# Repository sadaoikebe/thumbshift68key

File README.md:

## TS69 親指シフト入力用 68% キーボード

分割3uスペースキーをもつ 68% キーボード  

## 必要なもの

* 基板 (製造サービスなどに発注)
* Pro Micro
* ピンヘッダ12ピン×2
* 6x 鬼目ナットM3 Aタイプ(打ち込み) 深さ5.5mm [モノタロウ](https://www.monotaro.com/p/4175/4824/)
* 6x M3キャップボルト [モノタロウ](https://www.monotaro.com/p/2901/7687/)
* 69x キースイッチ
* スタビライザー (3x2u, 2x3u)
* キーキャップ 2x 3uスペース
* ガスケット (4mm幅×2mm厚のPoronやEVAフォームなどを貼る)
* ケース 3Dプリンタ [データ](case/)
* 定位板 3Dプリンタ もしくは業者にレーザーカッティングをお願いする [データ](plate/)

Pro Microは同等品のType-Cやコンスルー版などのほうが良いかも。MicroUSB版を使うならばコネクタモゲないようにエポキシ接着剤などで補強したほうがよい  

## 製造工程

Pro Microを裏側実装する関係で、実装の順番を間違えると面倒なことになる  
1. 基板にスタビライザーを取り付け
2. 基板にピンヘッダを半田付け
3. 周辺部分のキースイッチを取り付け
4. スタビライザーの動作確認 キースイッチを取り付けてキーキャップを実際に被せてスタビライザーが気持ちよく動くか確認。プレートの精度が十分よければこの手順は必要ないけど、3Dプリンタでプレートを自作する場合、しばしばスタビライザー軸が端に触れて動きが悪くなることがある。もし動きが悪い場合プレートの精度を見直すか、あるいはスタビライザーの動作が悪いキーが嵌まる部分のプレートを削って広げて遊びを作る。
5. キースイッチを全部取り付け
6. Pro Microを取り付け
7. キーキャップを取り付け
8. ケースに入れる

## キー配置

バックスペースキーの部分だけカスタマイズ可能だがそれ以外は固定。  
バックスペースキーの場所には2つのキーを割り当てて H*KBのような配置にすることもできる。  
今後親指キーに3u以外(2.75u, 2.25uなど) も使えるようにしたバージョンを作りたかったりはする。

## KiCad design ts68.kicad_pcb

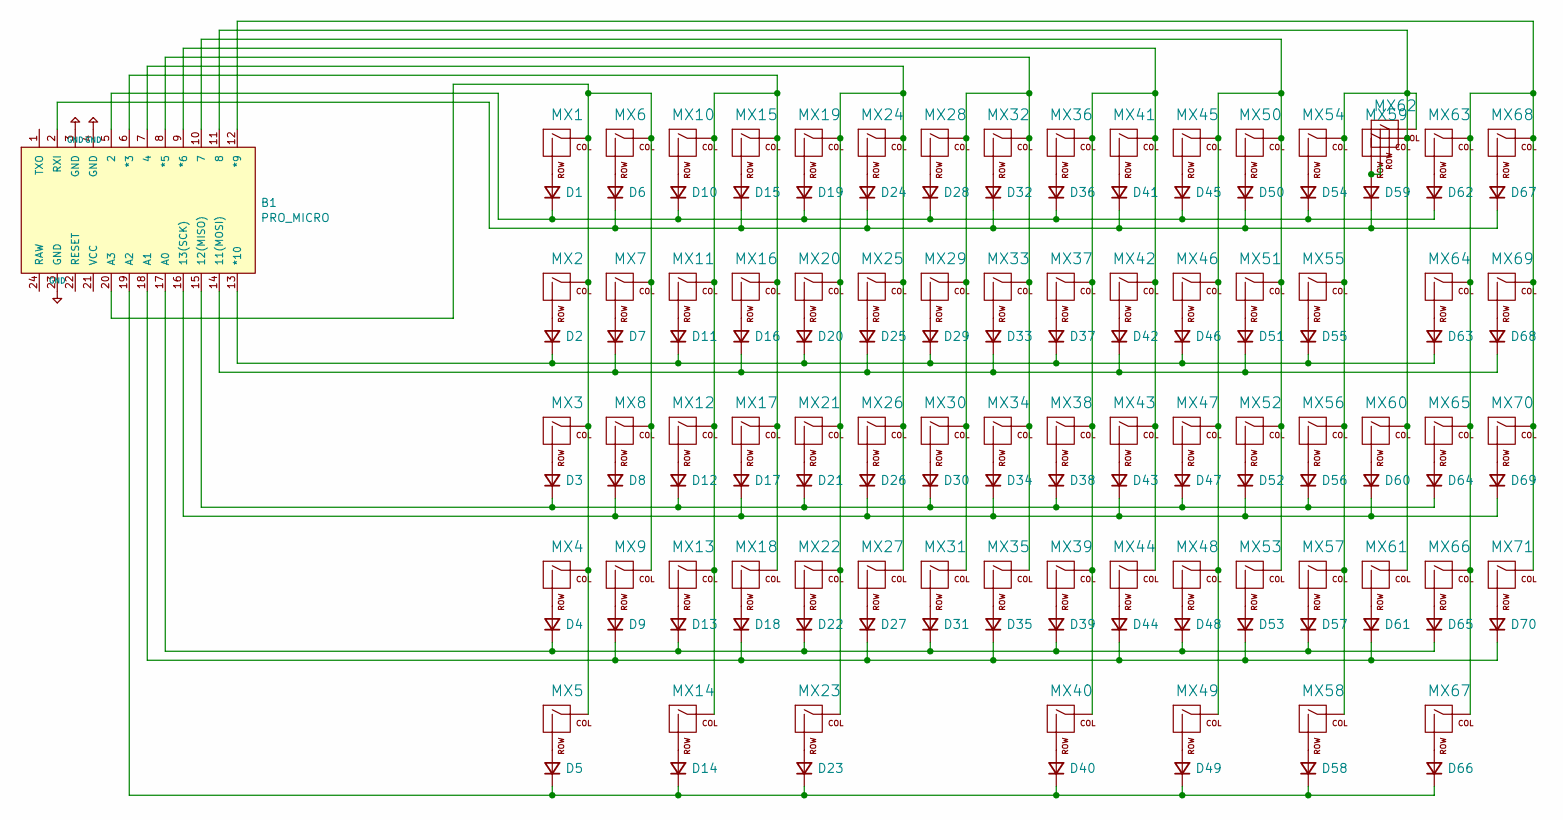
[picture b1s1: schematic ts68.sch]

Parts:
B1: PRO_MICRO; SPARKFUN_PRO_MICRO
D1, D2, D3, D4, D5, D6, D7, D8, D9, D10, D11, D12, D13, D14, D15, D16, D17, D18, D19, D20, D21, D22, D23, D24, D25, D26, D27, D28, D29, D30, D31, D32, D33, D34, D35, D36, D37, D38, D39, D40, D41, D42, D43, D44, D45, D46, D47, D48, D49, D50, D51, D52, D53, D54, D55, D56, D57, D58, D59, D60, D61, D62, D63, D64, D65, D66, D67, D68, D69, D70: D; D_SOD-123
MX1, MX6, MX7, MX8, MX10, MX11, MX12, MX13, MX15, MX16, MX17, MX18, MX19, MX20, MX21, MX22, MX24, MX25, MX26, MX27, MX28, MX29, MX30, MX31, MX32, MX33, MX34, MX35, MX36, MX37, MX38, MX39, MX41, MX42, MX43, MX44, MX45, MX46, MX47, MX48, MX50, MX51, MX52, MX53, MX54, MX55, MX56, MX58, MX59, MX61, MX63, MX65, MX66, MX67, MX68, MX69, MX70, MX71: MX-NoLED; MXOnly-1U-NoLED
MX2, MX64: MX-NoLED; MXOnly-1.5U-NoLED
MX3, MX57: MX-NoLED; MXOnly-1.75U-NoLED
MX4, MX60: MX-NoLED; MXOnly-2.25U-NoLED
MX5, MX9, MX14, MX49: MX-NoLED; MXOnly-1.25U-NoLED
MX23, MX40: MX-NoLED; MXOnly-3U-ReversedStabilizers-NoLED
MX62: MX-NoLED; MXOnly-2U-NoLED

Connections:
+5V: B1.3 (GND), B1.4 (GND), B1.23 (GND)
unnamed: B1.2 (RXI), D6.1 (K), D15.1 (K), D24.1 (K), D32.1 (K), D41.1 (K), D50.1 (K), D59.1 (K), D67.1 (K)
unnamed: B1.5 (2), D1.1 (K), D10.1 (K), D19.1 (K), D28.1 (K), D36.1 (K), D45.1 (K), D54.1 (K), D62.1 (K)
unnamed: B1.6 (*3), MX10.1 (COL), MX11.1 (COL), MX12.1 (COL), MX13.1 (COL), MX14.1 (COL), MX15.1 (COL), MX16.1 (COL), MX17.1 (COL), MX18.1 (COL)
unnamed: B1.7 (4), MX19.1 (COL), MX20.1 (COL), MX21.1 (COL), MX22.1 (COL), MX23.1 (COL), MX24.1 (COL), MX25.1 (COL), MX26.1 (COL), MX27.1 (COL)
unnamed: B1.8 (*5), MX28.1 (COL), MX29.1 (COL), MX30.1 (COL), MX31.1 (COL), MX32.1 (COL), MX33.1 (COL), MX34.1 (COL), MX35.1 (COL)
unnamed: B1.9 (*6), MX36.1 (COL), MX37.1 (COL), MX38.1 (COL), MX39.1 (COL), MX40.1 (COL), MX41.1 (COL), MX42.1 (COL), MX43.1 (COL), MX44.1 (COL)
unnamed: B1.10 (7), MX45.1 (COL), MX46.1 (COL), MX47.1 (COL), MX48.1 (COL), MX49.1 (COL), MX50.1 (COL), MX51.1 (COL), MX52.1 (COL), MX53.1 (COL)
unnamed: B1.11 (8), MX54.1 (COL), MX55.1 (COL), MX56.1 (COL), MX57.1 (COL), MX58.1 (COL), MX59.1 (COL), MX60.1 (COL), MX61.1 (COL), MX62.1 (COL)
unnamed: B1.12 (*9), MX63.1 (COL), MX64.1 (COL), MX65.1 (COL), MX66.1 (COL), MX67.1 (COL), MX68.1 (COL), MX69.1 (COL), MX70.1 (COL), MX71.1 (COL)
unnamed: B1.13 (*10), D2.1 (K), D11.1 (K), D20.1 (K), D29.1 (K), D37.1 (K), D46.1 (K), D55.1 (K), D63.1 (K)
unnamed: B1.14 (11(MOSI)), D7.1 (K), D16.1 (K), D25.1 (K), D33.1 (K), D42.1 (K), D51.1 (K), D68.1 (K)
unnamed: B1.15 (12(MISO)), D3.1 (K), D12.1 (K), D21.1 (K), D30.1 (K), D38.1 (K), D47.1 (K), D56.1 (K), D64.1 (K)
unnamed: B1.16 (13(SCK)), D8.1 (K), D17.1 (K), D26.1 (K), D34.1 (K), D43.1 (K), D52.1 (K), D60.1 (K), D69.1 (K)
unnamed: B1.17 (A0), D4.1 (K), D13.1 (K), D22.1 (K), D31.1 (K), D39.1 (K), D48.1 (K), D57.1 (K), D65.1 (K)
unnamed: B1.18 (A1), D9.1 (K), D18.1 (K), D27.1 (K), D35.1 (K), D44.1 (K), D53.1 (K), D61.1 (K), D70.1 (K)
unnamed: B1.19 (A2), D5.1 (K), D14.1 (K), D23.1 (K), D40.1 (K), D49.1 (K), D58.1 (K), D66.1 (K)
unnamed: B1.20 (A3), MX1.1 (COL), MX2.1 (COL), MX3.1 (COL), MX4.1 (COL), MX5.1 (COL), MX6.1 (COL), MX7.1 (COL), MX8.1 (COL), MX9.1 (COL)
unnamed: D1.2 (A), MX1.2 (ROW)
unnamed: D2.2 (A), MX2.2 (ROW)
unnamed: D3.2 (A), MX3.2 (ROW)
unnamed: D4.2 (A), MX4.2 (ROW)
unnamed: D5.2 (A), MX5.2 (ROW)
unnamed: D6.2 (A), MX6.2 (ROW)
unnamed: D7.2 (A), MX7.2 (ROW)
unnamed: D8.2 (A), MX8.2 (ROW)
unnamed: D9.2 (A), MX9.2 (ROW)
unnamed: D10.2 (A), MX10.2 (ROW)
unnamed: D11.2 (A), MX11.2 (ROW)
unnamed: D12.2 (A), MX12.2 (ROW)
unnamed: D13.2 (A), MX13.2 (ROW)
unnamed: D14.2 (A), MX14.2 (ROW)
unnamed: D15.2 (A), MX15.2 (ROW)
unnamed: D16.2 (A), MX16.2 (ROW)
unnamed: D17.2 (A), MX17.2 (ROW)
unnamed: D18.2 (A), MX18.2 (ROW)
unnamed: D19.2 (A), MX19.2 (ROW)
unnamed: D20.2 (A), MX20.2 (ROW)
unnamed: D21.2 (A), MX21.2 (ROW)
unnamed: D22.2 (A), MX22.2 (ROW)
unnamed: D23.2 (A), MX23.2 (ROW)
unnamed: D24.2 (A), MX24.2 (ROW)
unnamed: D25.2 (A), MX25.2 (ROW)
unnamed: D26.2 (A), MX26.2 (ROW)
unnamed: D27.2 (A), MX27.2 (ROW)
unnamed: D28.2 (A), MX28.2 (ROW)
unnamed: D29.2 (A), MX29.2 (ROW)
unnamed: D30.2 (A), MX30.2 (ROW)
unnamed: D31.2 (A), MX31.2 (ROW)
unnamed: D32.2 (A), MX32.2 (ROW)
unnamed: D33.2 (A), MX33.2 (ROW)
unnamed: D34.2 (A), MX34.2 (ROW)
unnamed: D35.2 (A), MX35.2 (ROW)
unnamed: D36.2 (A), MX36.2 (ROW)
unnamed: D37.2 (A), MX37.2 (ROW)
unnamed: D38.2 (A), MX38.2 (ROW)
unnamed: D39.2 (A), MX39.2 (ROW)
unnamed: D40.2 (A), MX40.2 (ROW)
unnamed: D41.2 (A), MX41.2 (ROW)
unnamed: D42.2 (A), MX42.2 (ROW)
unnamed: D43.2 (A), MX43.2 (ROW)
unnamed: D44.2 (A), MX44.2 (ROW)
unnamed: D45.2 (A), MX45.2 (ROW)
unnamed: D46.2 (A), MX46.2 (ROW)
unnamed: D47.2 (A), MX47.2 (ROW)
unnamed: D48.2 (A), MX48.2 (ROW)
unnamed: D49.2 (A), MX49.2 (ROW)
unnamed: D50.2 (A), MX50.2 (ROW)
unnamed: D51.2 (A), MX51.2 (ROW)
unnamed: D52.2 (A), MX52.2 (ROW)
unnamed: D53.2 (A), MX53.2 (ROW)
unnamed: D54.2 (A), MX54.2 (ROW)
unnamed: D55.2 (A), MX55.2 (ROW)
unnamed: D56.2 (A), MX56.2 (ROW)
unnamed: D57.2 (A), MX57.2 (ROW)
unnamed: D58.2 (A), MX58.2 (ROW)
unnamed: D59.2 (A), MX59.2 (ROW), MX62.2 (ROW)
unnamed: D60.2 (A), MX60.2 (ROW)
unnamed: D61.2 (A), MX61.2 (ROW)
unnamed: D62.2 (A), MX63.2 (ROW)
unnamed: D63.2 (A), MX64.2 (ROW)
unnamed: D64.2 (A), MX65.2 (ROW)
unnamed: D65.2 (A), MX66.2 (ROW)
unnamed: D66.2 (A), MX67.2 (ROW)
unnamed: D67.2 (A), MX68.2 (ROW)
unnamed: D68.2 (A), MX69.2 (ROW)
unnamed: D69.2 (A), MX70.2 (ROW)
unnamed: D70.2 (A), MX71.2 (ROW)

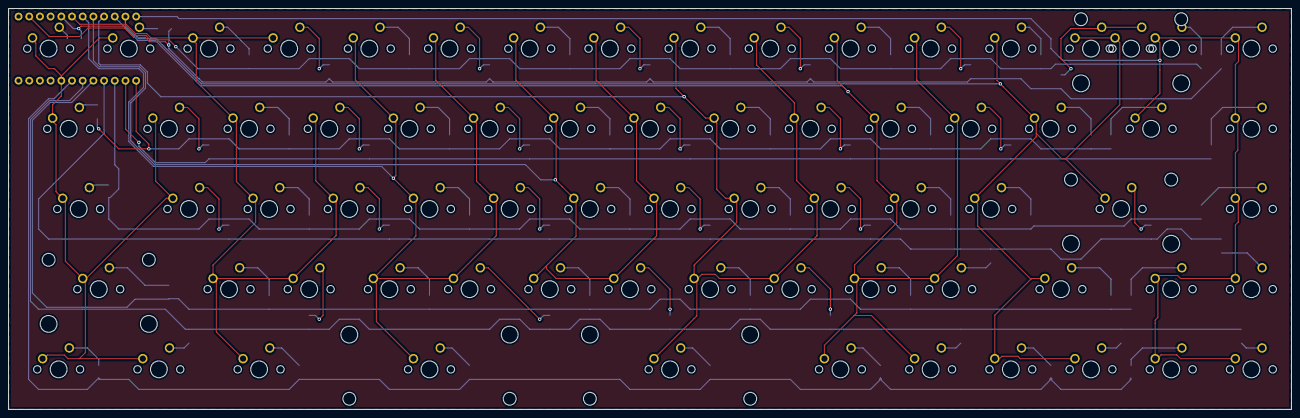
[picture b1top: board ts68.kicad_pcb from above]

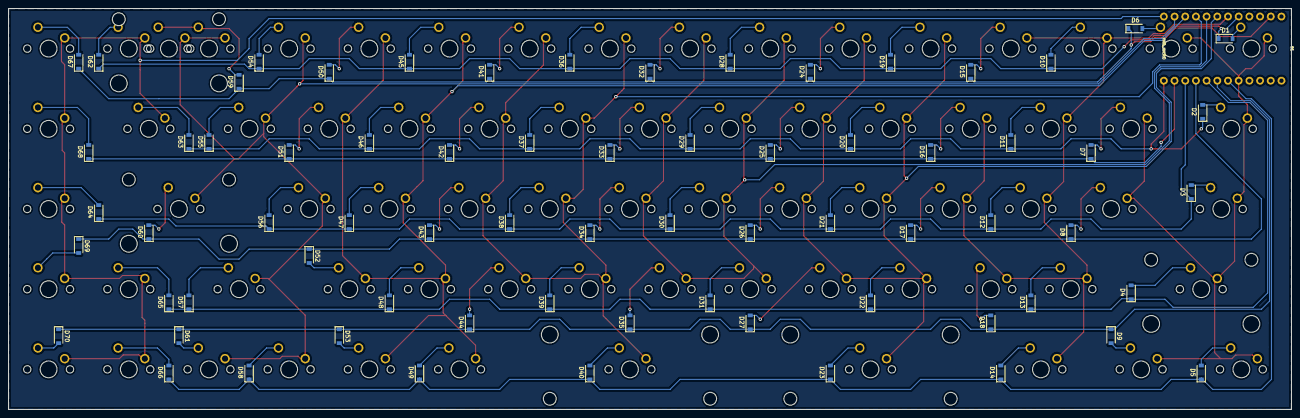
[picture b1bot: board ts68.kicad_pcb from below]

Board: 2 copper layers, 304.8 x 95.2 mm, 142 parts (71 on the bottom side), 88 nets.

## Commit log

2021-09-01 add plate
2021-09-01 add case
2021-09-01 tune alignment play
2021-09-01 bottom section thinning
2021-09-02 hole diameter
2021-09-02 case inflated
2021-09-02 plate inflated
2021-09-11 first successful version
2021-09-11 case and plate readme
2021-09-11 add description
2021-09-14 add laser cutting plate
2021-09-14 Create LICENSE
2021-09-16 update documents
2021-09-18 add link for bolts
2021-09-19 add link for version 3 case
2021-09-26 wrong link
